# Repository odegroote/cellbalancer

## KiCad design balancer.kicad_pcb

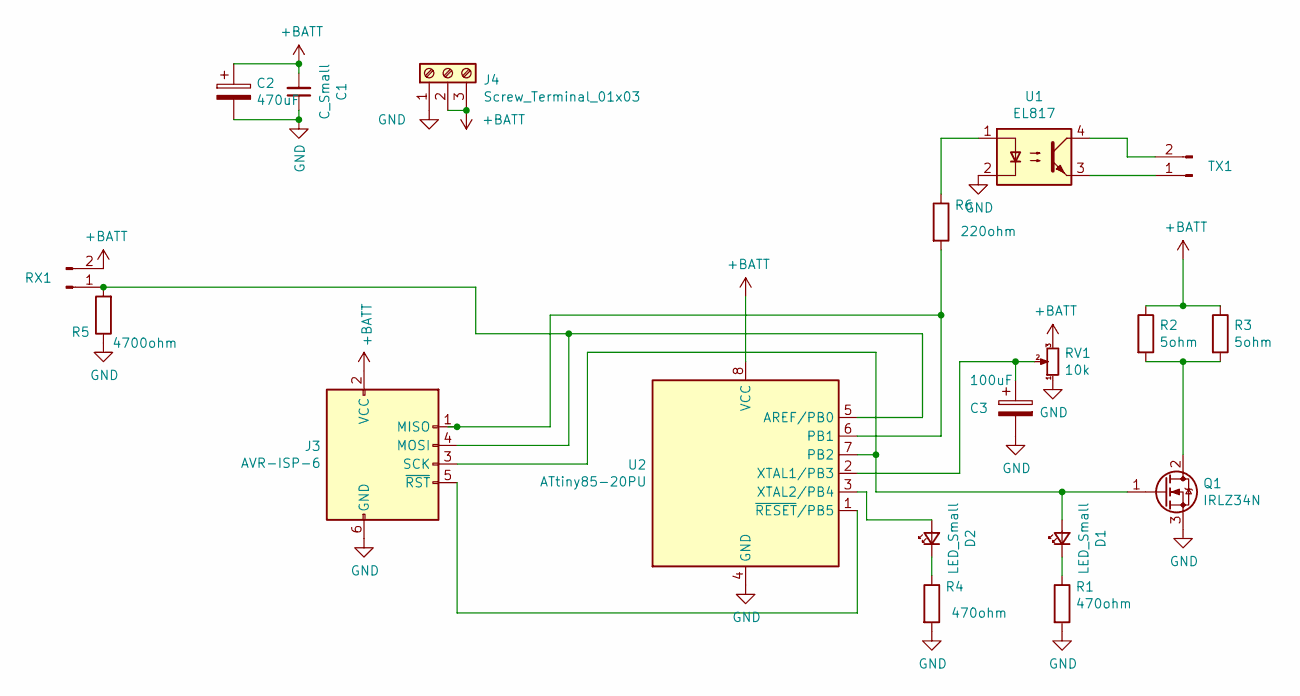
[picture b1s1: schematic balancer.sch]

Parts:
C1: C_Small; C_Disc_D4.7mm_W2.5mm_P5.00mm
C2: 470uF; CP_Radial_D5.0mm_P2.50mm
C3: 100uF; CP_Radial_D5.0mm_P2.50mm
D1, D2: LED_Small; LED_D3.0mm
J3: AVR-ISP-6; PinHeader_2x03_P2.54mm_Vertical
J4: Screw_Terminal_01x03; TerminalBlock_Phoenix_MKDS-1,5-3-5.08_1x03_P5.08mm_Horizont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
Q1: IRLZ34N; TO-220-3_Vertical
R1, R4: 470ohm; R_Axial_DIN0204_L3.6mm_D1.6mm_P7.62mm_Horizontal
R2, R3: 5ohm; R_Axial_Power_L48.0mm_W12.5mm_P55.88mm
R5: 4700ohm; R_Axial_DIN0204_L3.6mm_D1.6mm_P7.62mm_Horizontal
R6: 220ohm; R_Axial_DIN0204_L3.6mm_D1.6mm_P7.62mm_Horizontal
RV1: 10k; Potentiometer_Bourns_3296W_Vertical
RX1: Conn_01x02_Male; JST_XH_B02B-XH-A_02x2.50mm_Straight
TX1: Conn_01x02_Male; TerminalBlock_TE_282834-2_1x02_P2.54mm_Horizontal
U1: EL817; DIP-4_W7.62mm
U2: ATtiny85-20PU; DIP-8_W7.62mm

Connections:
+BATT: C1.2, C2.1, J3.2 (VCC), J4.2, J4.3, R2.1, R3.1, RV1.3, RX1.2, U2.8 (VCC)
GND: C1.1, C2.2, C3.2, J3.6 (GND), J4.1, Q1.3 (S), R1.2, R4.2, R5.1, RV1.1, U1.2, U2.4 (GND)
unnamed: C3.1, RV1.2, U2.2 (XTAL1/PB3)
unnamed: D1.1 (K), R1.1
unnamed: D1.2 (A), J3.3 (SCK), Q1.1 (G), U2.7 (PB2)
unnamed: D2.1 (K), R4.1
unnamed: D2.2 (A), U2.3 (XTAL2/PB4)
unnamed: J3.1 (MISO), R6.2, U2.6 (PB1)
unnamed: J3.4 (MOSI), R5.2, RX1.1, U2.5 (AREF/PB0)
unnamed: J3.5 (~RST), U2.1 (~RESET~/PB5)
unnamed: Q1.2 (D), R2.2, R3.2
unnamed: R6.1, U1.1
unnamed: TX1.1, U1.3
unnamed: TX1.2, U1.4

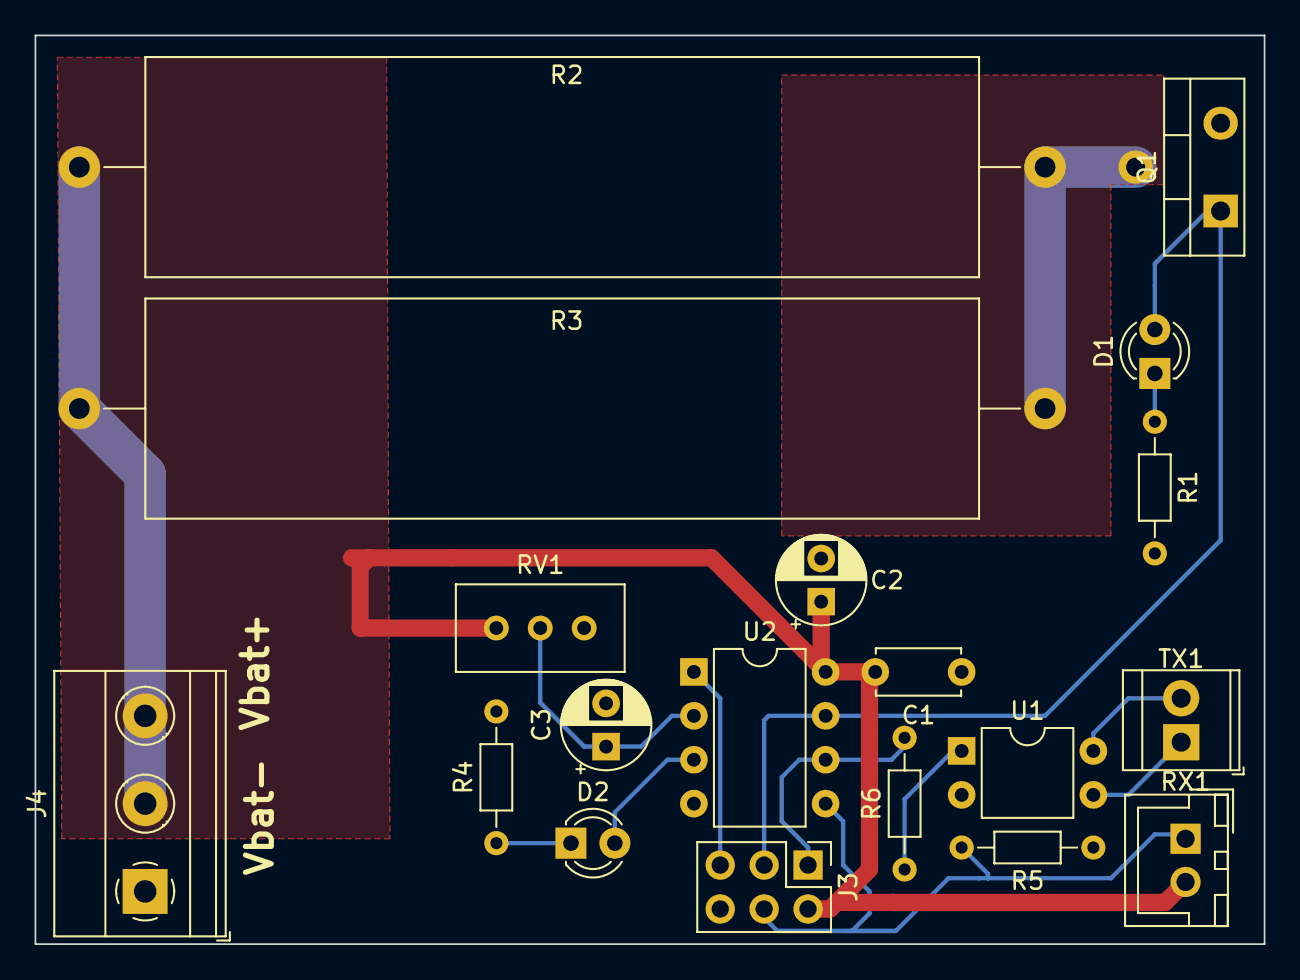
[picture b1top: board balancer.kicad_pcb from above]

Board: 2 copper layers, 71.1 x 52.6 mm, 19 parts (0 on the bottom side), 14 nets.

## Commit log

2022-10-05 changed VBATT connector from 2 GND to 2 VBATT
2022-10-23 removed junction in schema
